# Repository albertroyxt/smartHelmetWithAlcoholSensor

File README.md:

# smartHelmetWithAlcoholSensor
It is a project based on Arduino RF communication along with Alcohol Sensor, Provided by sparkfun.
It is having Two sections. Transmit and Recieve. Transmit section is attached with Helmet and reciever section with the vehicle.

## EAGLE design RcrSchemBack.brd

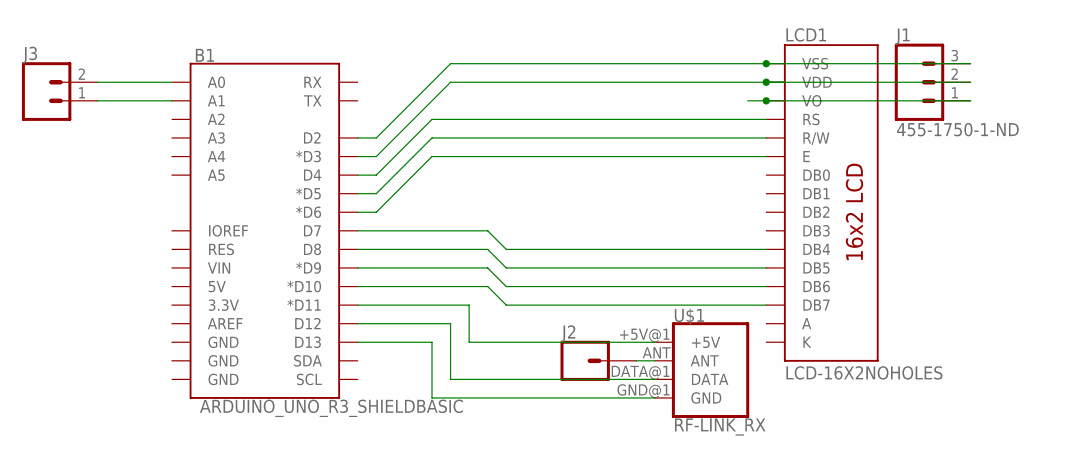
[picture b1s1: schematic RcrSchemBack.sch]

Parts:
B1: ARDUINO_UNO_R3_SHIELDBASIC; UNO_R3_SHIELD
J1: 455-1750-1-ND; 1X03
J2: CONN_01; 1X01
J3: CONN_02; 1X02
LCD1: LCD-16X2NOHOLES; LCD-16X2_NOHOLESNOSILK
U$1: RF-LINK_RX

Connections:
A: LCD1.15 (A)
K: LCD1.16 (K)
unnamed: B1.D2, J1.3, LCD1.1 (VSS)
unnamed: B1.D3 (*D3), J1.2, LCD1.2 (VDD)
unnamed: B1.D4, LCD1.4 (RS)
unnamed: B1.D5 (*D5), LCD1.5 (R/W)
unnamed: B1.D6 (*D6), LCD1.6 (E)
unnamed: B1.D7, LCD1.11 (DB4)
unnamed: B1.D8, LCD1.12 (DB5)
unnamed: B1.D9 (*D9), LCD1.13 (DB6)
unnamed: B1.D10 (*D10), LCD1.14 (DB7)
unnamed: J2.1, U$1.ANT
unnamed: B1.D11 (*D11), U$1.+5V@1 (+5V)
unnamed: B1.D12, U$1.DATA@1 (DATA)
unnamed: B1.D13, U$1.GND@1 (GND)
unnamed: J1.1, LCD1.3 (VO)
unnamed: B1.A0, J3.2
unnamed: B1.A1, J3.1

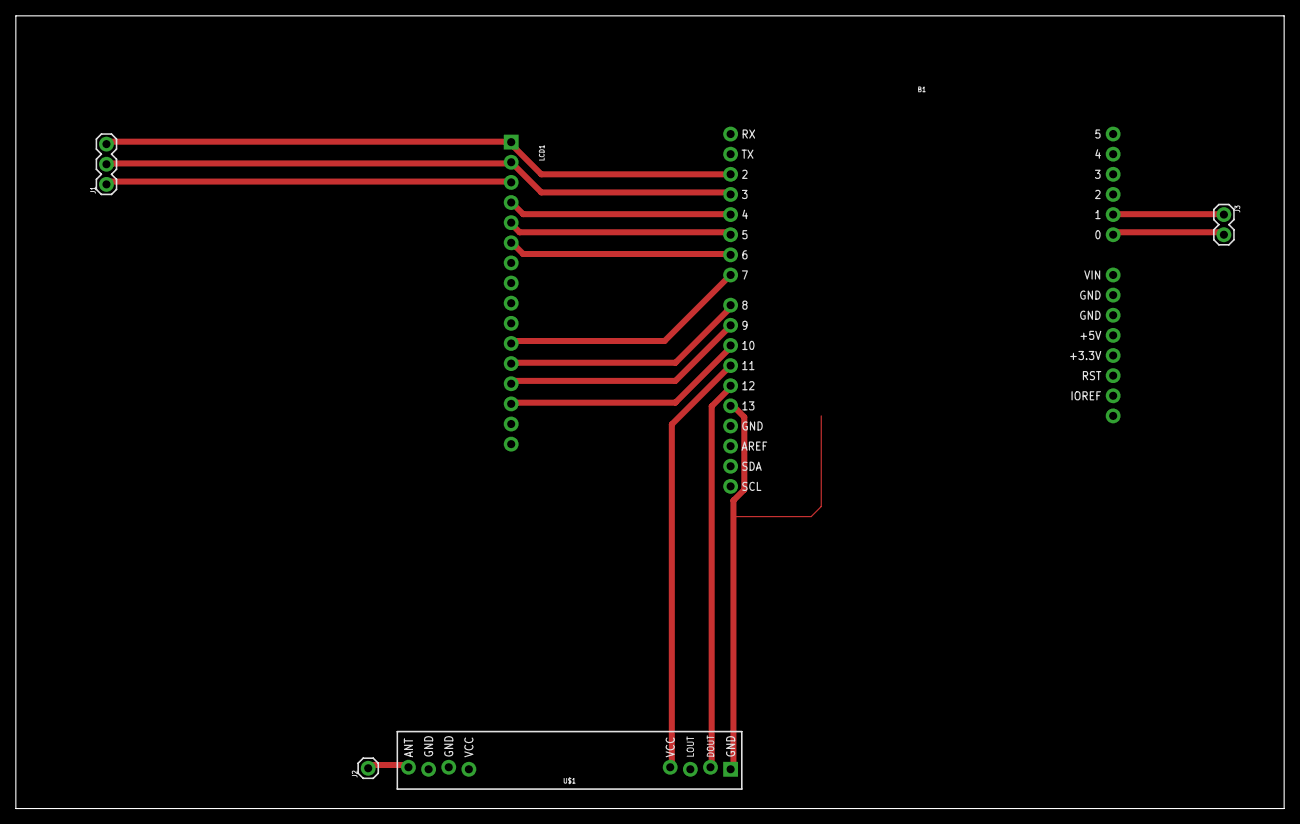
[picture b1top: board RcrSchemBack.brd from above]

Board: 2 copper layers, 160.0 x 100.0 mm, 6 parts (0 on the bottom side), 16 nets.

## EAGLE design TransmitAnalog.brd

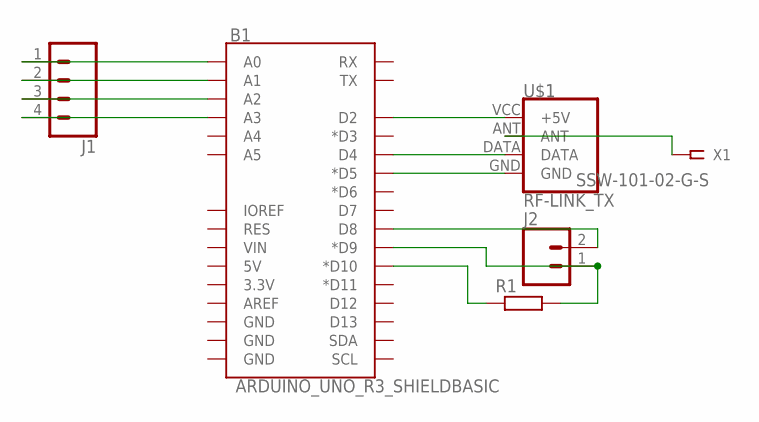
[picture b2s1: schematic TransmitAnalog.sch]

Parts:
B1: ARDUINO_UNO_R3_SHIELDBASIC; UNO_R3_SHIELD
J1: CONN_04; 1X04
J2: CONN_02; 1X02
R1: R-EU_0204/7; 0204/7
U$1: RF-LINK_TX
X1: SSW-101-02-G-S

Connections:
unnamed: B1.A0, J1.1
unnamed: B1.A1, J1.2
unnamed: B1.A2, J1.3
unnamed: B1.A3, J1.4
unnamed: B1.D2, U$1.VCC (+5V)
unnamed: B1.D4, U$1.DATA
unnamed: B1.D5 (*D5), U$1.GND
unnamed: U$1.ANT, X1.1
unnamed: B1.D8, J2.2
unnamed: B1.D9 (*D9), J2.1, R1.2
unnamed: B1.D10 (*D10), R1.1

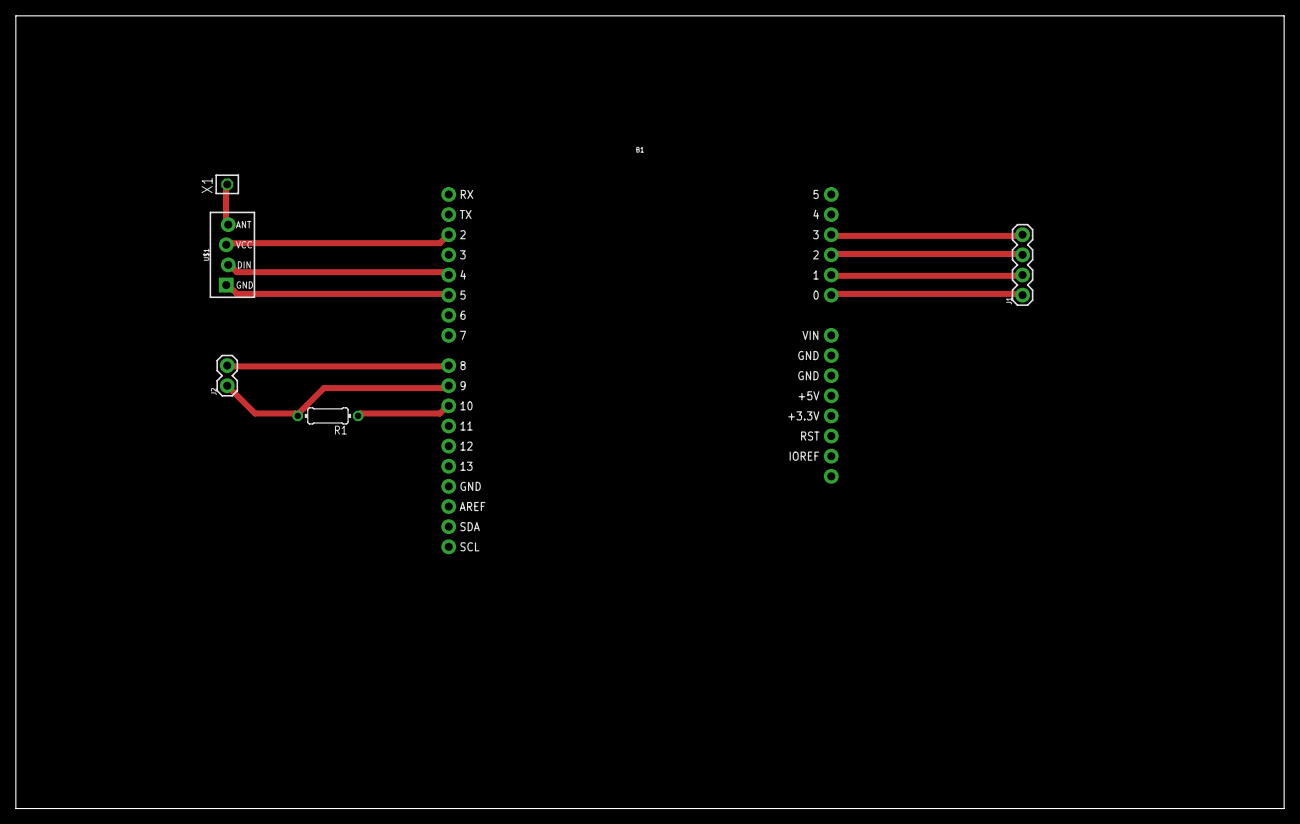
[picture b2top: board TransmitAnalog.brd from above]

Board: 2 copper layers, 160.0 x 100.0 mm, 6 parts (0 on the bottom side), 11 nets.

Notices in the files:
parts and their libraries:
SparkFun-Boards: Licensing: Creative Commons ShareAlike 4.0 International - https://creativecommons.org/licenses/by-sa/4.0
